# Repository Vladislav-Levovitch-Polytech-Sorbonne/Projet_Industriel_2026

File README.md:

# Projet_Industriel_2026

## Project Description - AI-Driven Autonomous Mobility Platform

This project focuses on the development of a fully autonomous mobility platform, built with an industrial engineering approach and strongly centered on artificial intelligence.

The objective is to design an embedded intelligent system capable of perceiving its environment, understanding spatial contexts, and navigating autonomously using modern AI methodologies.  
The work emphasizes **autonomous decision-making**, **environment perception**, **real-time control**, and **system reliability**, reflecting challenges found in advanced robotics and intelligent mobility applications.

The platform integrates:

- A **Raspberry Pi** running high-level AI logic and perception pipelines in **Python**,  
- An **STM32 microcontroller** running real-time control and actuator management in **C++**,  
- A modular hardware architecture including LiDAR, camera, motor control, and telemetry.

### Artificial Intelligence & Perception  
- Real-time computer vision for feature extraction and spatial understanding  
- Machine learning pipelines for perception, prediction, and autonomous control  
- Reinforcement and imitation learning for adaptive navigation behaviors  
- Sensor fusion (LiDAR + camera + onboard telemetry)  

### Embedded Intelligence & Real-Time Control  
- Deterministic control loops for steering and propulsion  
- Low-latency sensor acquisition and decoding  
- STM32 firmware ensuring consistent timing and reliable actuation  
- Dynamic modeling to characterize turning radius, constraints, and latency budgets  

### System Architecture & Integration  
- Modular hardware architecture for sensing, actuation, and computation  
- Integration of LiDAR, camera modules, servo controllers, and embedded processors  
- Spatial mapping using LiDAR-based reconstruction  
- Iterative testing and validation for robust real-world behavior  

This platform serves as a realistic environment to develop and evaluate industrial-grade AI and embedded autonomy techniques.

---

## ⚙️ Repository Structure

The repository is organized as follows:

+ 🗂️ **[`Useful_Resources`](./Docs/Useful_Resources)** - Contains visual resources and diagrams used in the documentation (FSM, sequence diagrams, architecture, etc.).

+ ⚖️​ **`LICENSE`** : This project is licensed under the GNU GPL v3.

---

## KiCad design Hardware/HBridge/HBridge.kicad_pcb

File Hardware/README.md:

# Projet_Industriel_2026
📜 Project Description

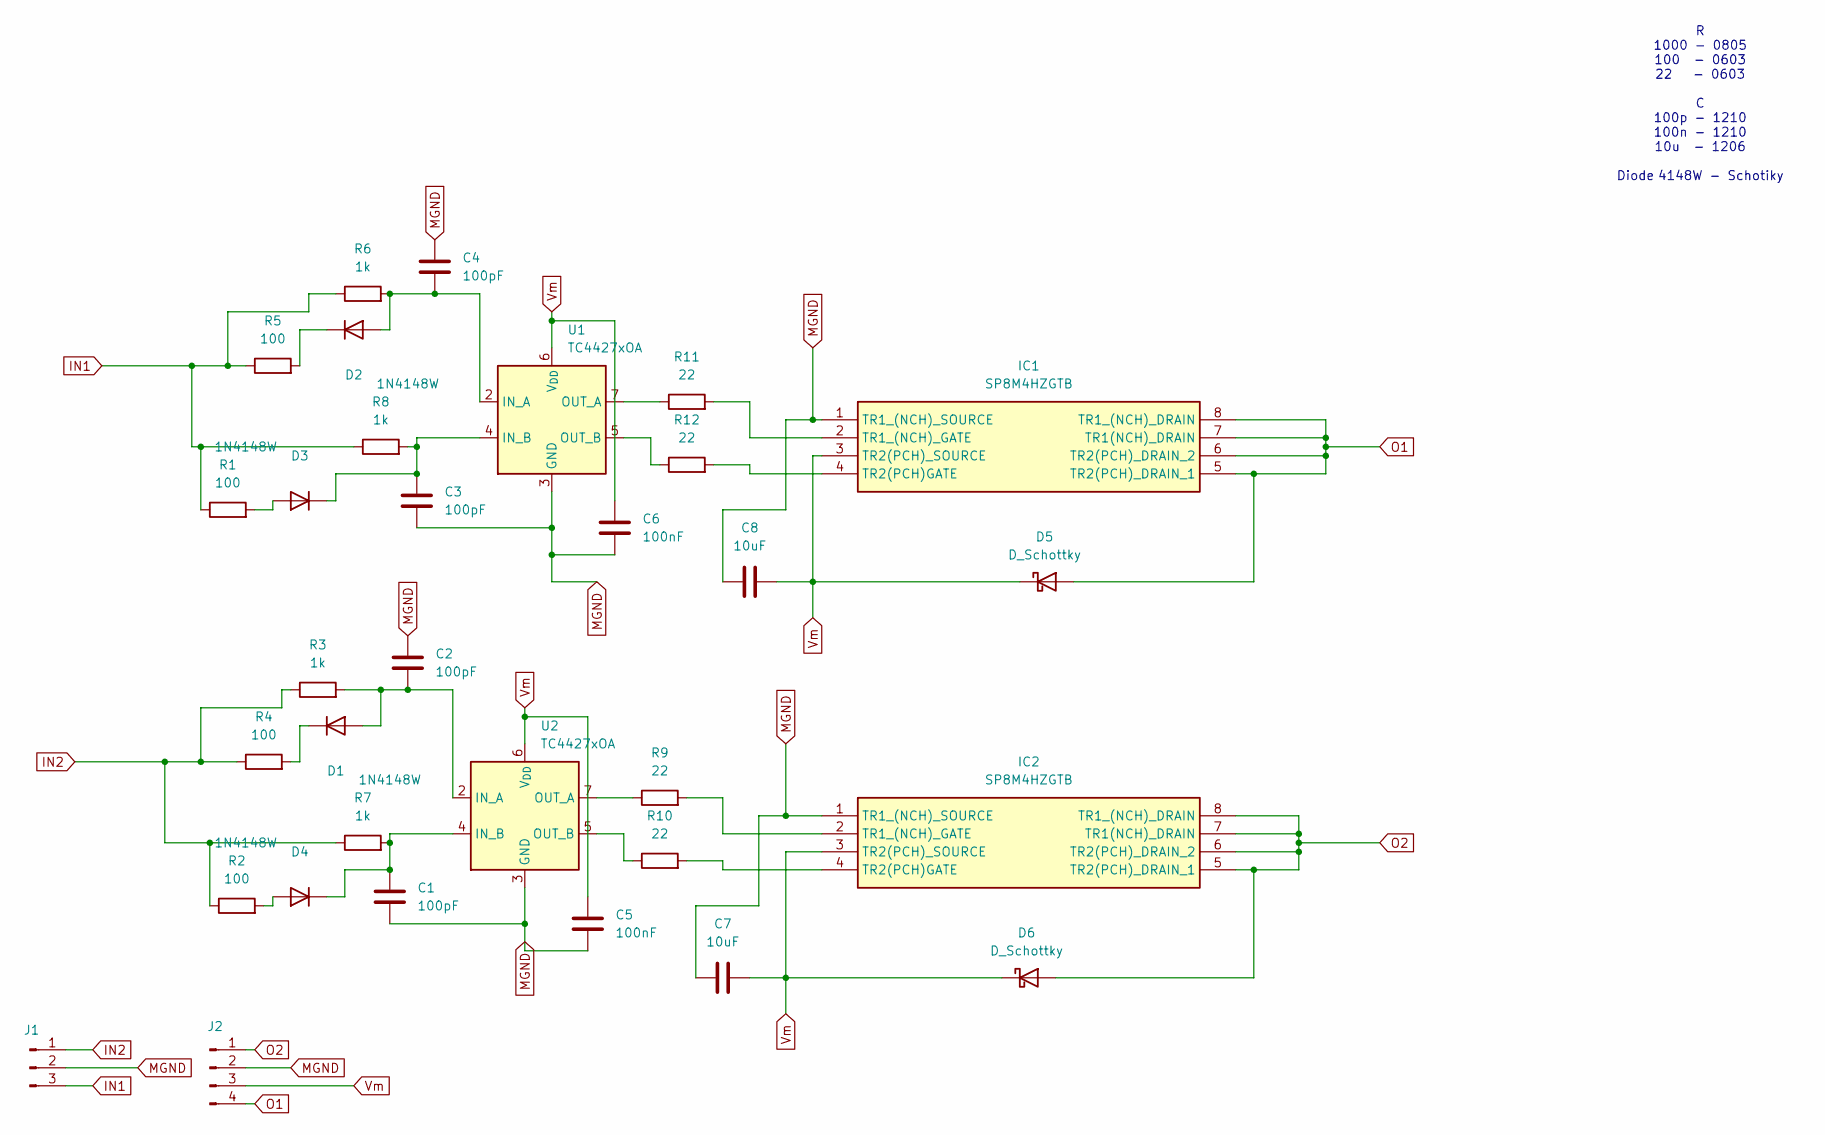
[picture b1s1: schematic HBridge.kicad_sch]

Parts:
C1, C2, C3, C4: 100pF; C_1210_3225Metric_Pad1.33x2.70mm_HandSolder
C5, C6: 100nF; C_Axial_L3.8mm_D2.6mm_P7.50mm_Horizontal
C7, C8: 10uF; C_Axial_L3.8mm_D2.6mm_P7.50mm_Horizontal
D1, D2, D3, D4: 1N4148W; D_SOD-123
D5, D6: D_Schottky; TO-220-2_Vertical
IC1, IC2: SP8M4HZGTB; SOIC127P600X175-8N; Manufacturer_Part_Number SP8M4HZGTB
J1: Conn_01x03_Pin; JST_XH_B3B-XH-A_1x03_P2.50mm_Vertical
J2: Conn_01x04_Pin; PhoenixContact_MSTBA_2,5_4-G-5,08_1x04_P5.08mm_Horizontal
R1, R2, R4, R5: 100; R_0603_1608Metric_Pad0.98x0.95mm_HandSolder
R3, R6, R7, R8: 1k; R_0508_1220Metric_Pad1.12x2.15mm_HandSolder
R9, R10, R11, R12: 22; R_0603_1608Metric_Pad0.98x0.95mm_HandSolder
U1, U2: TC4427xOA; SOIC-8_3.9x4.9mm_P1.27mm

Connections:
IN1: J1.3, R1.1, R5.1, R6.1, R8.1
IN2: J1.1, R2.1, R3.1, R4.1, R7.1
MGND: C1.1, C2.1, C3.1, C4.1, C5.2, C6.2, C7.2, C8.2, IC1.1 (TR1_(NCH)_SOURCE), IC2.1 (TR1_(NCH)_SOURCE), J1.2, J2.2, U1.3 (GND), U2.3 (GND)
unnamed: C2.2, D1.2 (A), R3.2, U2.2 (IN_A)
unnamed: D1.1 (K), R4.2
unnamed: C4.2, D2.2 (A), R6.2, U1.2 (IN_A)
unnamed: D2.1 (K), R5.2
unnamed: D3.2 (A), R1.2
unnamed: C3.2, D3.1 (K), R8.2, U1.4 (IN_B)
unnamed: D4.2 (A), R2.2
unnamed: C1.2, D4.1 (K), R7.2, U2.4 (IN_B)
unnamed: IC1.2 (TR1_(NCH)_GATE), R11.2
unnamed: IC1.4 (TR2(PCH)GATE), R12.2
unnamed: IC2.2 (TR1_(NCH)_GATE), R9.2
unnamed: IC2.4 (TR2(PCH)GATE), R10.2
unnamed: R11.1, U1.7 (OUT_A)
unnamed: R12.1, U1.5 (OUT_B)
unnamed: R9.1, U2.7 (OUT_A)
unnamed: R10.1, U2.5 (OUT_B)
O1: D5.2 (A), IC1.5 (TR2(PCH)_DRAIN_1), IC1.6 (TR2(PCH)_DRAIN_2), IC1.7 (TR1(NCH)_DRAIN), IC1.8 (TR1_(NCH)_DRAIN), J2.4
O2: D6.2 (A), IC2.5 (TR2(PCH)_DRAIN_1), IC2.6 (TR2(PCH)_DRAIN_2), IC2.7 (TR1(NCH)_DRAIN), IC2.8 (TR1_(NCH)_DRAIN), J2.1
Vm: C5.1, C6.1, C7.1, C8.1, D5.1 (K), D6.1 (K), IC1.3 (TR2(PCH)_SOURCE), IC2.3 (TR2(PCH)_SOURCE), J2.3, U1.6 (V_{DD}), U2.6 (V_{DD})

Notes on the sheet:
R 1000 - 0805 100 - 0603 22 - 0603 C 100p - 1210 100n - 1210 10u - 1206 Diode 4148W - Schotiky

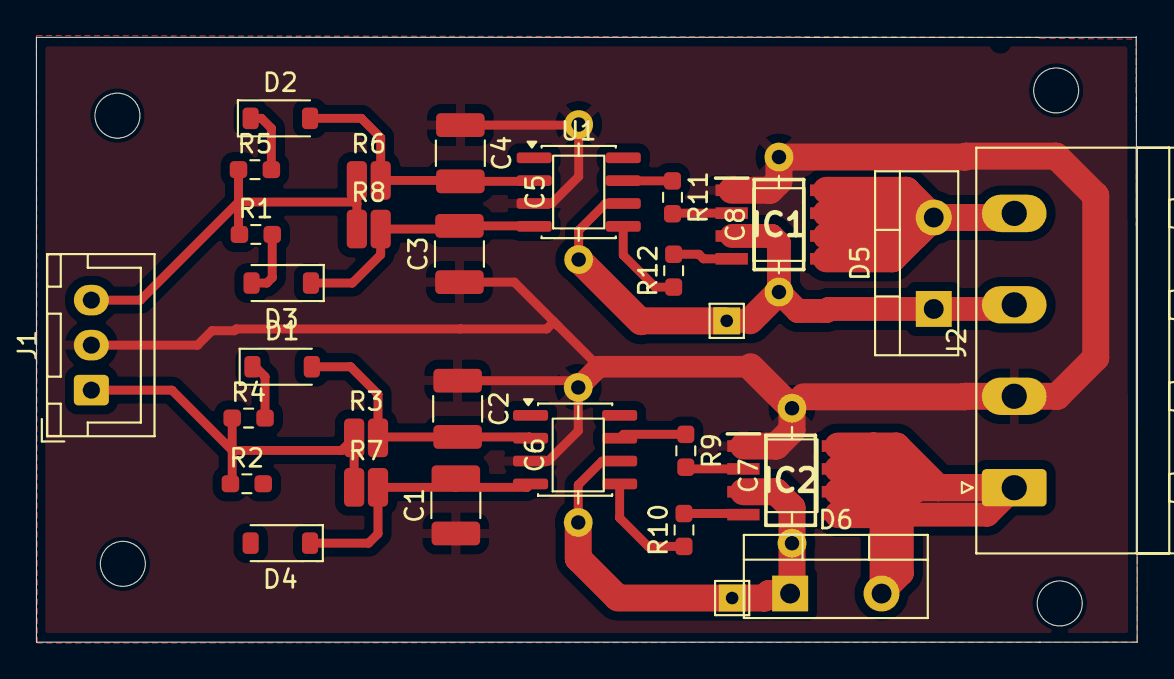
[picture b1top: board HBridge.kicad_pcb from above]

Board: 2 copper layers, 61.2 x 33.7 mm, 32 parts (0 on the bottom side), 22 nets.

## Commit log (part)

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2025-11-21 Add deployment workflow and enhance documentation for AI-driven autonomous mobility platform
2025-11-21 Fix paths in deployment workflow for documentation installation and deployment
2025-11-21 Deployed 8c9ca9c with MkDocs version: 1.6.1
2025-11-21 add fiche CDCF(Ref #4)
2025-11-21 Deployed 0ebe741 with MkDocs version: 1.6.1
2025-11-25 Bilan IO V1
2025-12-03 STM32L432KC_v1
2025-12-06 feat: Create First version of H bridge pcb
2025-12-10 Add test reports for BNO055 IMU and SHARP GP2Y0A21YK0F sensors
    - Created a comprehensive test report for the BNO055 IMU sensor, detailing hardware configuration, software implementation, testing procedures, results, and conclusions.
    - Added a test report for the SHARP GP2Y0A21YK0F infrared distance sensor, including ADC-DMA data acquisition, voltage conversion accuracy, distance calculation, and boundary condition testing.
2025-12-10 更新 .gitignore，添加对 Thumbs.db 和 nul 文件的忽略
2025-12-18 -Add servo motor test report, calibration guide, and troubleshooting checklist -Add ESC driver
2026-01-14 Add Phase 1 Vehicle Test Report documenting testing procedures, results, and system architecture for CoVAPSy 2025 autonomous vehicle
2026-01-14 Add Schottky diode component to HBridge schematic
    - Introduced a new Schottky diode symbol with reference designators D5 and D6.
    - Updated properties including Value, Footprint, and Description for the new diode.
    - Added necessary junctions and wires to integrate the diode into the existing circuit.
    - Ensured the new component is included in the BOM and is visible on the board.
2026-01-16 Add CoVAPSy SPI communication library and interactive test tool
    - Implemented the CoVAPSySPI class for SPI communication with the CoVAPSy autonomous vehicle, including frame building, response parsing, and command methods.
    - Added CRC-16/MODBUS checksum calculation for data integrity.
    - Created an interactive command-line tool for testing SPI communication, allowing users to control the vehicle, query status, and view statistics.
    - Included detailed documentation and usage examples in both the library and the interactive tool.
2026-01-16 修正 README.md 中的硬件连接说明，更新 STM32 NSS 引脚为 PA4
2026-01-16 update PA4
2026-01-16 Docs: Update vehicle test reports and pin configuration (Ref #13)
2026-01-16 Logique du système de contrôle du véhicule
2026-01-19 reset update (Ref #14)
2026-01-19 更新SPI硬件调试模式为启用，并优化CoVAPSySPI类中的命令发送和响应处理逻辑
2026-01-19 优化CoVAPSySPI类中的命令发送和响应处理逻辑，增加延迟以确保STM32处理命令后再发送心跳以获取响应
2026-02-08 Files for simulation
2026-02-08 Refactor code structure for improved readability and maintainability
2026-05-29 updateal
2026-06-22 Add FreeRTOS (CMSIS-V2) to CoVAPSy_L432KC firmware
    - Add FreeRTOS middleware with CMSIS-RTOS V2 interface
    - Switch HAL timebase from SysTick to TIM6
    - Create 3 tasks: ControlTask (50Hz), DebugTask (1Hz), defaultTask
    - Create SPIDataSemaphore for ISR-to-task notification
    - Implement Vehicle and SPI initialization before scheduler start
    - Release semaphore from HAL_SPI_TxRxCpltCallback (ISR-safe)
2026-06-22 Deployed c2713aa with MkDocs version: 1.6.1
